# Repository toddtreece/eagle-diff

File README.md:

# Visual Diff Tool for CadSoft Eagle 6

This tool is a work in progress.  More information will be available as the project progresses.

*Requires node v0.10.21 or greater.*

````bash
$ npm install -g grunt-cli
$ git clone git@github.com:toddtreece/eagle-diff.git
$ cd eagle-diff
$ npm install
$ grunt serve
````

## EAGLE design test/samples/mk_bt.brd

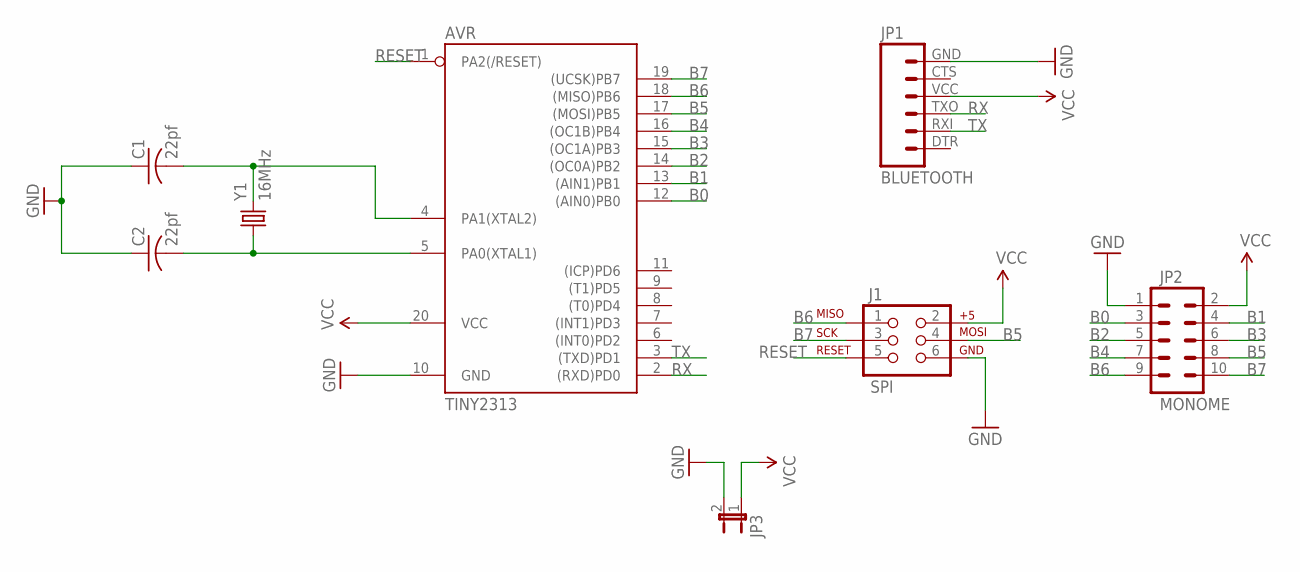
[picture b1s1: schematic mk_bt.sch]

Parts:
AVR: TINY2313; DIL20
C1, C2: 22pf; C025-025X050
J1: SPI; 2X3
JP1: BLUETOOTH; FTDI_BASIC
JP2: MONOME; 2X5-SHROUDED
JP3: JUMPER-2PTH; 1X02
Y1: 16MHz; HC49US

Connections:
B0: AVR.12 ((AIN0)PB0), JP2.3
B1: AVR.13 ((AIN1)PB1), JP2.4
B2: AVR.14 ((OC0A)PB2), JP2.5
B3: AVR.15 ((OC1A)PB3), JP2.6
B4: AVR.16 ((OC1B)PB4), JP2.7
B5: AVR.17 ((MOSI)PB5), J1.4, JP2.8
B6: AVR.18 ((MISO)PB6), J1.1, JP2.9
B7: AVR.19 ((UCSK)PB7), J1.3, JP2.10
GND: AVR.10 (GND), C1.1, C2.1, J1.6, JP1.GND (6), JP2.1, JP3.2
unnamed: AVR.5 (PA0(XTAL1)), C2.2, Y1.1
unnamed: AVR.4 (PA1(XTAL2)), C1.2, Y1.2
RESET: AVR.1 (PA2(/RESET)), J1.5
RX: AVR.2 ((RXD)PD0), JP1.TXO (3)
TX: AVR.3 ((TXD)PD1), JP1.RXI (2)
VCC: AVR.20 (VCC), J1.2, JP1.VCC (4), JP2.2, JP3.1

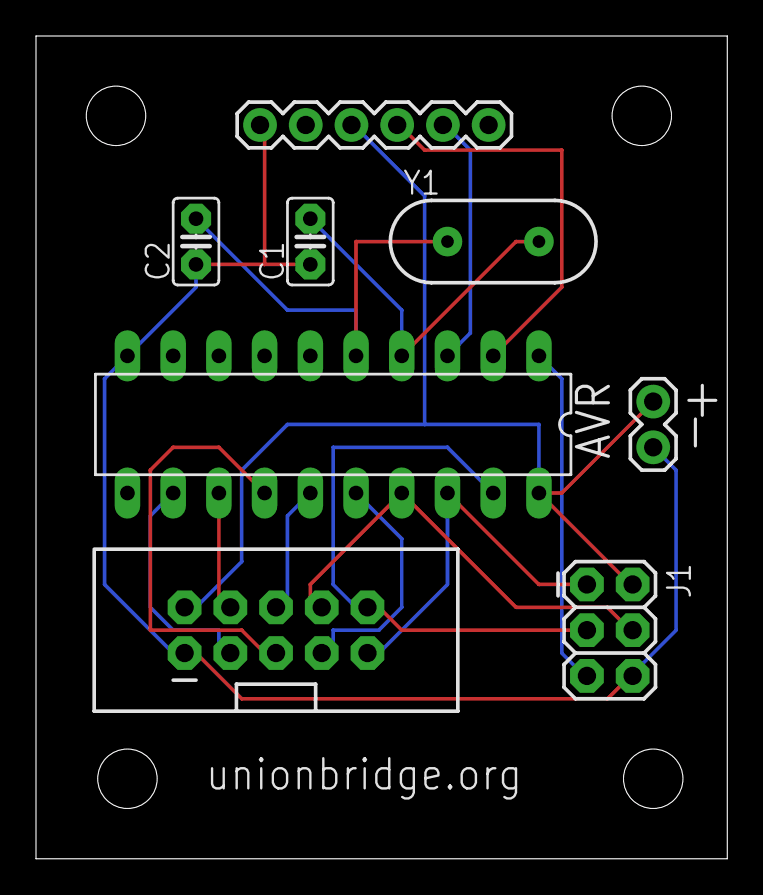
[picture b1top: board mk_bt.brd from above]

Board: 2 copper layers, 38.4 x 45.7 mm, 12 parts (0 on the bottom side), 15 nets.

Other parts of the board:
U$1, U$2, U$3, U$4: STAND-OFF

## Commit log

2012-07-26 added a few more object types
2012-07-26 schematic spec finished. ...i think
2012-07-27 added js compiler & object defaults
2012-07-31 wip: started thinking about how to draw stuff
2013-11-05 adds npm package.json
2013-11-05 adds js compile helper
2013-11-05 js reserved words w/ dot syntax won't compile with gcc
2013-11-05 adds sample board and schematic
2013-11-05 adds bower package file
2013-11-05 adds simple index.html & css
2013-11-05 adds assets to gitignore
2013-11-05 adds simple test server`
2013-11-05 adds 'npm start' shortcut to start the test server
2013-11-05 adds .bowerrc file
2013-11-05 Adds simple instructions to README.md
2013-11-05 adds bower to npm package
2013-11-05 adds a few log messages to compiler & test-server
2013-11-05 renames compiler
2013-11-06 start purging external libs
2013-11-06 removes bower and jquery
2013-11-06 adds utility function to clear canvas
2013-11-06 adds build and test folder
2013-11-06 adds grunt
2013-11-06 starting the process of removing jquery for xml parsing
2013-11-06 adds closepath to Eagle.js
2013-11-07 rewrite moveTo & lineTo to use native canvas methods
2013-11-07 use grunt for js compression & concatenation
2013-11-07 removes node-minify
2013-11-07 adds watcher & server to grunt file
2013-11-07 kills old test server
2013-11-07 renames Eagle.each to Eagle.eachNode
2013-11-07 strip jquery++
2013-11-07 finished removing jquery requirement
2013-11-07 adds connect to dev dependencies
2013-11-07 readme++
2013-11-07 adds grunt-cli to the npm package
2013-11-07 fix canvas size for testing
2013-11-08 don't render hidden & inactive layers
2013-11-08 store a reference to parent on each object
2013-11-08 updates copyright info
2013-11-08 adds grunt module for connect webserver
2013-11-08 replace custom webserver task with connect module
2013-11-15 adds Eagle.Color util and the default eagle palettes
2013-11-23 updates readme

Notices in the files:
parts and their libraries:
SparkFun: Licensing: CC v3.0 Share-Alike You are welcome to use this library for commercial purposes.
